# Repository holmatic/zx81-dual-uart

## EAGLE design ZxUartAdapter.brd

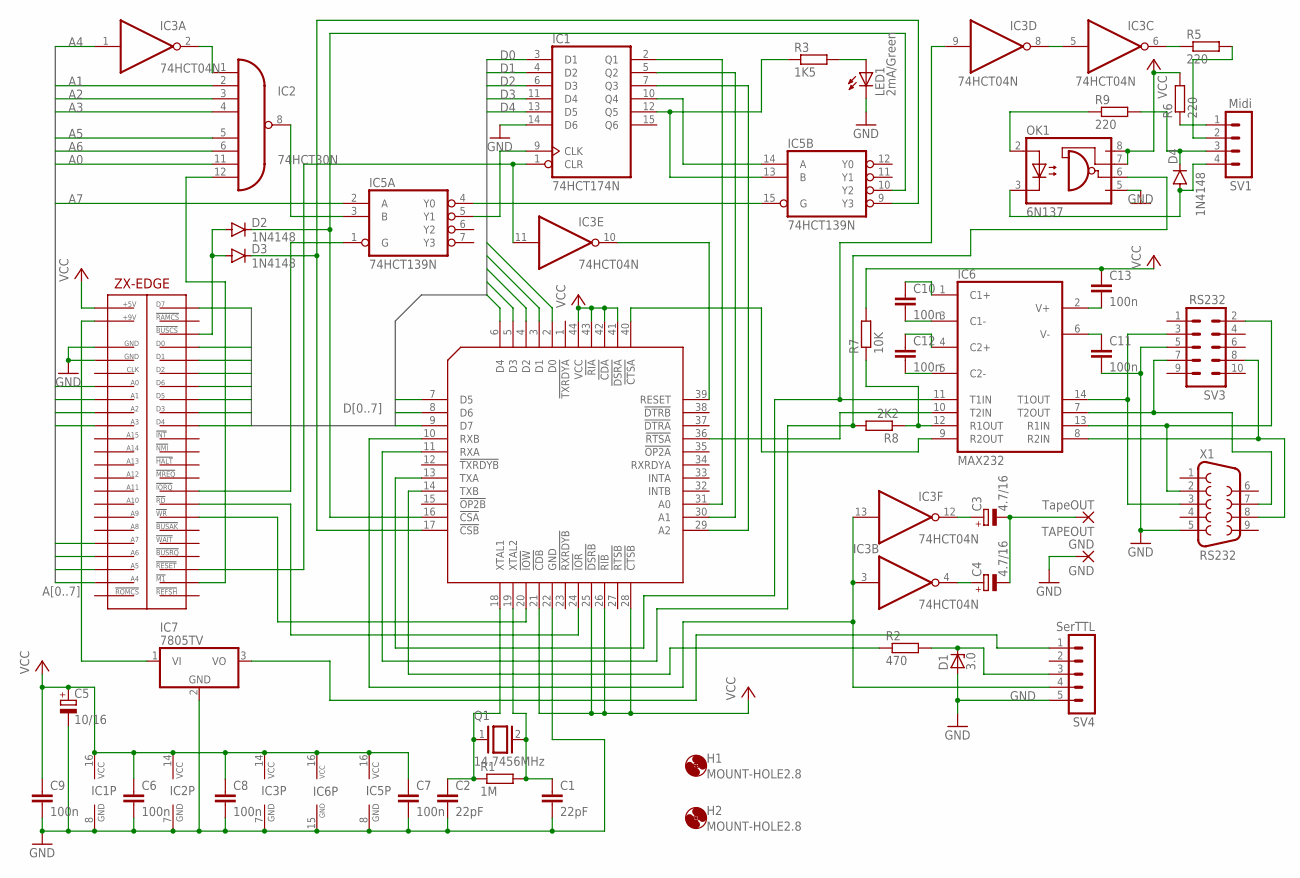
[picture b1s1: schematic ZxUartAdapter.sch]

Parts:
C1, C2: 22pF; C025-025X050
C3, C4: 4.7/16; E5-5
C5: 10/16; E5-6
C6, C7, C8, C9, C10, C11, C12, C13: 100n; C050-024X044
D1: 3.0; ZDIO-7.5
D2, D3, D4: 1N4148; DO35-7
GND: GND; 2,15/1,0
H1, H2: MOUNT-HOLE2.8; 2,8
IC1: 74HCT174N; DIL16
IC2: 74HCT30N; DIL14
IC3: 74HCT04N; DIL14
IC4: XR16C2850; S44
IC5: 74HCT139N; DIL16
IC6: MAX232; DIL16
IC7: 7805TV; TO220V
LED1: 2mA/Green; LED3MM
OK1: 6N137; DIL08
Q1: 14.7456MHz; QS
R1: 1M; 0207/12
R2: 470; 0207/12
R3: 1K5; 0207/12
R5, R6, R9: 220; 0207/12
R7: 10K; 0207/12
R8: 2K2; 0207/12
SV1: Midi; MA04-1
SV3: RS232; MA05-2
SV4: SerTTL; MA05-1
TAPEOUT: TapeOUT; 2,15/1,0
U$1: ZX-EDGEZX96; ZX-EDGE64
X1: RS232; F09HP

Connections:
A0: IC2.11 (I6), U$1.A21 (A0)
A1: IC2.2 (I1), U$1.A20 (A1)
A2: IC2.3 (I2), U$1.A19 (A2)
A3: IC2.4 (I3), U$1.A18 (A3)
A4: IC3.1 (I), U$1.A6 (A4)
A5: IC2.5 (I4), U$1.A7 (A5)
A6: IC2.6 (I5), U$1.A8 (A6)
A7: IC5.2 (A), U$1.A9 (A7)
D0: IC1.3 (D1), IC4.2 (D0), U$1.C24 (D0)
D1: IC1.4 (D2), IC4.3 (D1), U$1.C23 (D1)
D2: IC1.6 (D3), IC4.4 (D2), U$1.C22 (D2)
D3: IC1.11 (D4), IC4.5 (D3), U$1.C19 (D3)
D4: IC1.13 (D5), IC4.6 (D4), U$1.C18 (D4)
D5: IC4.7 (D5), U$1.C20 (D5)
D6: IC4.8 (D6), U$1.C21 (D6)
D7: IC4.9 (D7), U$1.C27 (D7)
GND: C1.2, C2.2, C5.-, C6.2, C7.2, C8.2, C9.2, C11.2, D1.A, GND.1, IC1.8 (GND), IC1.14 (D6), IC2.7 (GND), IC3.7 (GND), IC4.22 (GND), IC5.8 (GND), IC6.15 (GND), IC7.2 (GND), LED1.K (C), OK1.5 (GND), SV3.5, SV4.5, U$1.A23 (GND2), U$1.A24 (GND1), X1.5
unnamed: IC2.1 (I0), IC3.2 (O)
unnamed: IC2.12 (I7), U$1.C6 (!M1)
unnamed: IC5.1 (G), U$1.C13 (!IORQ)
unnamed: IC2.8 (O), IC5.3 (B)
unnamed: IC1.9 (CLK), IC5.5 (Y1)
unnamed: IC5.4 (Y0), IC5.15 (G)
unnamed: IC1.10 (Q4), IC5.14 (A)
unnamed: IC1.12 (Q5), IC5.13 (B), R3.1
unnamed: IC1.1 (CLR), IC3.11 (I), U$1.C7 (!RESET)
unnamed: C13.2, IC6.2 (V+)
unnamed: IC1.2 (Q1), IC4.31 (A0)
unnamed: IC1.5 (Q2), IC4.30 (A1)
unnamed: IC1.7 (Q3), IC4.29 (A2)
unnamed: C11.1, IC6.6 (V-)
unnamed: IC3.10 (O), IC4.39 (RESET)
unnamed: D2.C, IC4.16 (!CSA), IC5.10 (Y2)
unnamed: D3.C, IC4.17 (!CSB), IC5.9 (Y3)
unnamed: IC4.20 (!IOW), U$1.C11 (!WR)
unnamed: IC4.24 (!IOR), U$1.C12 (!RD)
unnamed: C1.1, IC4.19 (XTAL2), Q1.2, R1.2
unnamed: C2.1, IC4.18 (XTAL1), Q1.1, R1.1
unnamed: D2.A, D3.A, U$1.C25 (!BUSCS)
unnamed: C10.2, IC6.3 (C1-)
unnamed: C10.1, IC6.1 (C1+)
unnamed: C12.2, IC6.5 (C2-)
unnamed: C12.1, IC6.4 (C2+)
unnamed: IC4.14 (TXB), R2.1
unnamed: IC6.13 (R1IN), SV3.2, X1.2
unnamed: IC3.9 (I), IC4.13 (TXA), IC6.11 (T1IN)
unnamed: IC3.5 (I), IC3.8 (O)
unnamed: D4.A, OK1.3 (C), SV1.4
unnamed: IC3.6 (O), R5.1
unnamed: R6.1, SV1.1
unnamed: R5.2, SV1.2
unnamed: IC4.11 (RXA), OK1.6 (VO), R8.2
unnamed: IC6.12 (R1OUT), R7.1, R8.1
unnamed: OK1.2 (A), R9.1
unnamed: D4.C, R9.2, SV1.3
unnamed: C3.+, IC3.12 (O)
unnamed: C4.+, IC3.4 (O)
unnamed: C3.-, C4.-, TAPEOUT.1
unnamed: IC3.3 (I), IC3.13 (I), IC4.10 (RXB), SV4.4
unnamed: D1.C, R2.2, SV4.3
unnamed: IC4.36 (!RTSA), IC6.10 (T2IN)
unnamed: IC6.14 (T1OUT), SV3.3, X1.3
unnamed: IC6.7 (T2OUT), SV3.7, X1.7
unnamed: IC6.8 (R2IN), SV3.8, X1.8
unnamed: IC4.40 (!CTSA), IC6.9 (R2OUT)
unnamed: LED1.A, R3.2
unnamed: IC7.1 (VI), U$1.A26 (+9)
unnamed: IC7.3 (VO), SV4.1
VCC: C5.+, C6.1, C7.1, C8.1, C9.1, C13.1, IC1.16 (VCC), IC2.14 (VCC), IC3.14 (VCC), IC4.21 (!CDB), IC4.25 (!DSRB), IC4.26 (!RIB), IC4.28 (!CTSB), IC4.41 (!DSRA), IC4.42 (!CDA), IC4.43 (!RIA), IC4.44 (VCC), IC5.16 (VCC), IC6.16 (VCC), OK1.7 (VE), OK1.8 (VCC), R6.2, R7.2, U$1.A27 (+5)

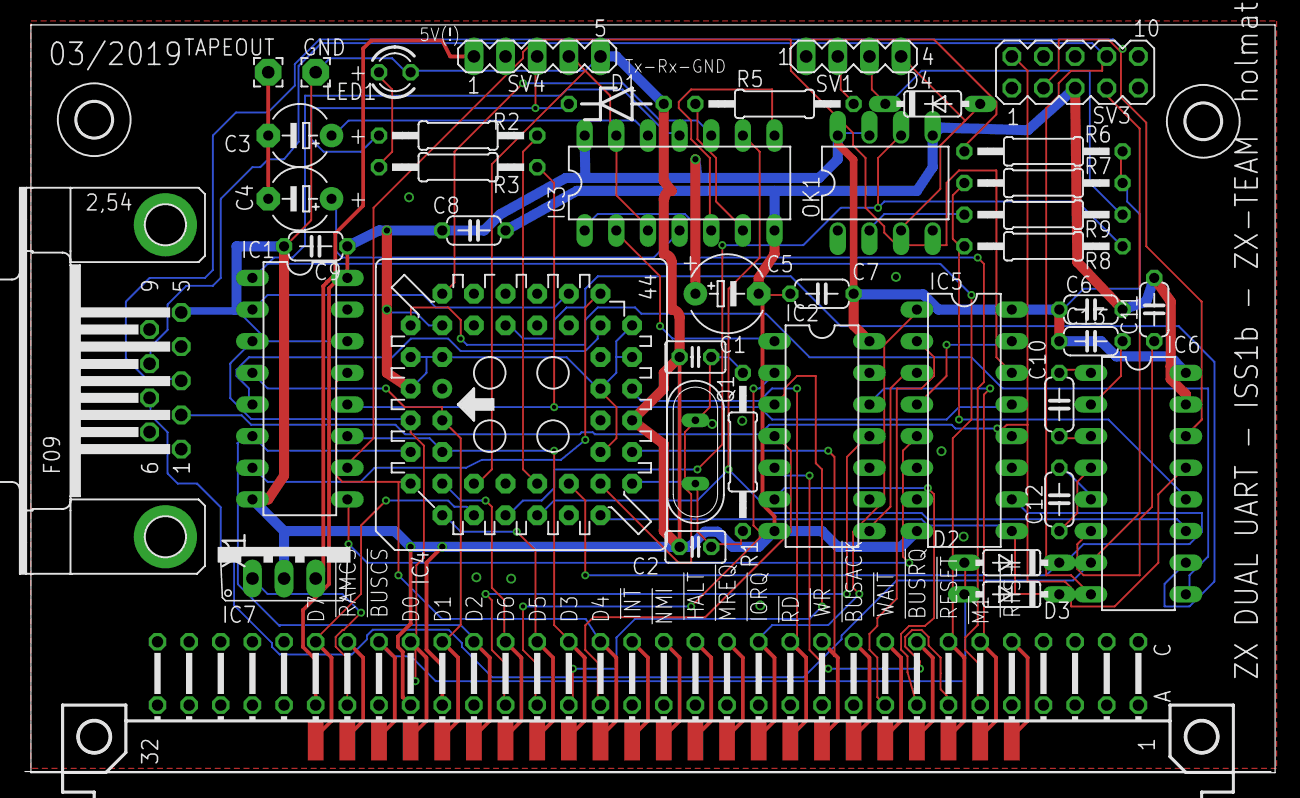
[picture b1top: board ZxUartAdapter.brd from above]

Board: 2 copper layers, 100.4 x 60.0 mm, 44 parts (0 on the bottom side), 69 nets.

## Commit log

2019-04-05 PDF Schematics added
2019-04-08 PDF pcb and partlist added
